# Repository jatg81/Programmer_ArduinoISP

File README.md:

# Programmer_ArduinoISP

This programmer allows to download bootloader and programs to the microprocessor ATMEGA128P (TQFP package).

It has four leds indicator:
  - Blue:   Heartbeat
  - Red:    Error
  - Yellow: Program mode (sending program)
  - Green:  Test led connected to D8

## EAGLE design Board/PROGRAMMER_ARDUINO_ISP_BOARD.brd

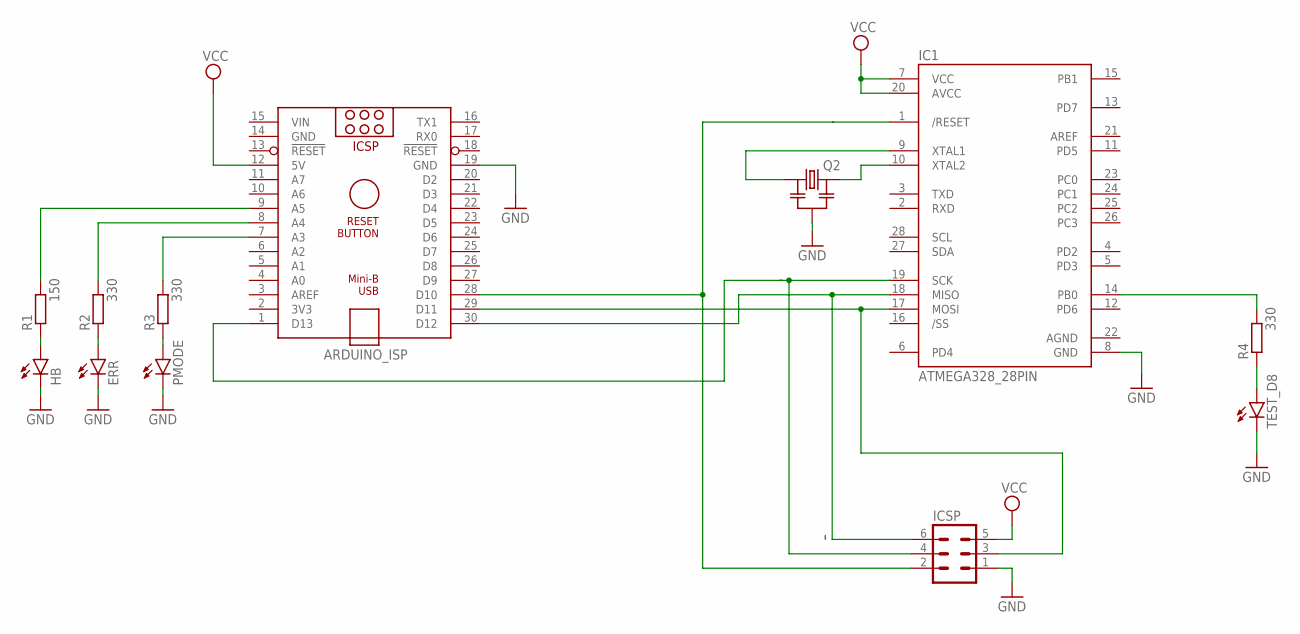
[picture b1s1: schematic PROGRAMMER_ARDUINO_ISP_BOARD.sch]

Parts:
ARDUINO_ISP: ARDUINO_NANO
ERR: LED3MM
HB: LED3MM
IC1: ATMEGA328_28PIN; DIL28-3-R
ICSP: MA03-2
PMODE: LED3MM
Q2: RESONATOR-MURATACST_CE; RESONATOR_MURATA2
R1: 150; R0805
R2, R3, R4: 330; R0805
TEST_D8: 330; LED3MM

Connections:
AGND: IC1.22 (AGND)
GND: ARDUINO_ISP.14 (GND), ARDUINO_ISP.19 (GND), ERR.K (C), HB.K (C), IC1.8 (GND), ICSP.1, PMODE.K (C), Q2.2, TEST_D8.K (C)
unnamed: IC1.9 (XTAL1), Q2.1
unnamed: IC1.10 (XTAL2), Q2.3
unnamed: ARDUINO_ISP.29 (D11), IC1.17 (MOSI), ICSP.3
unnamed: ARDUINO_ISP.30 (D12), IC1.18 (MISO), ICSP.6
unnamed: HB.A, R1.1
unnamed: R4.1, TEST_D8.A
unnamed: ERR.A, R2.1
unnamed: PMODE.A, R3.1
unnamed: ARDUINO_ISP.7 (A3), R3.2
unnamed: ARDUINO_ISP.8 (A4), R2.2
unnamed: ARDUINO_ISP.9 (A5), R1.2
unnamed: IC1.14 (PB0), R4.2
unnamed: ARDUINO_ISP.28 (D10), IC1.1 (/RESET), ICSP.2
unnamed: ARDUINO_ISP.1 (D13), IC1.19 (SCK), ICSP.4
VCC: ARDUINO_ISP.12 (5V), IC1.7 (VCC), IC1.20 (AVCC), ICSP.5
VIN: ARDUINO_ISP.15 (VIN)

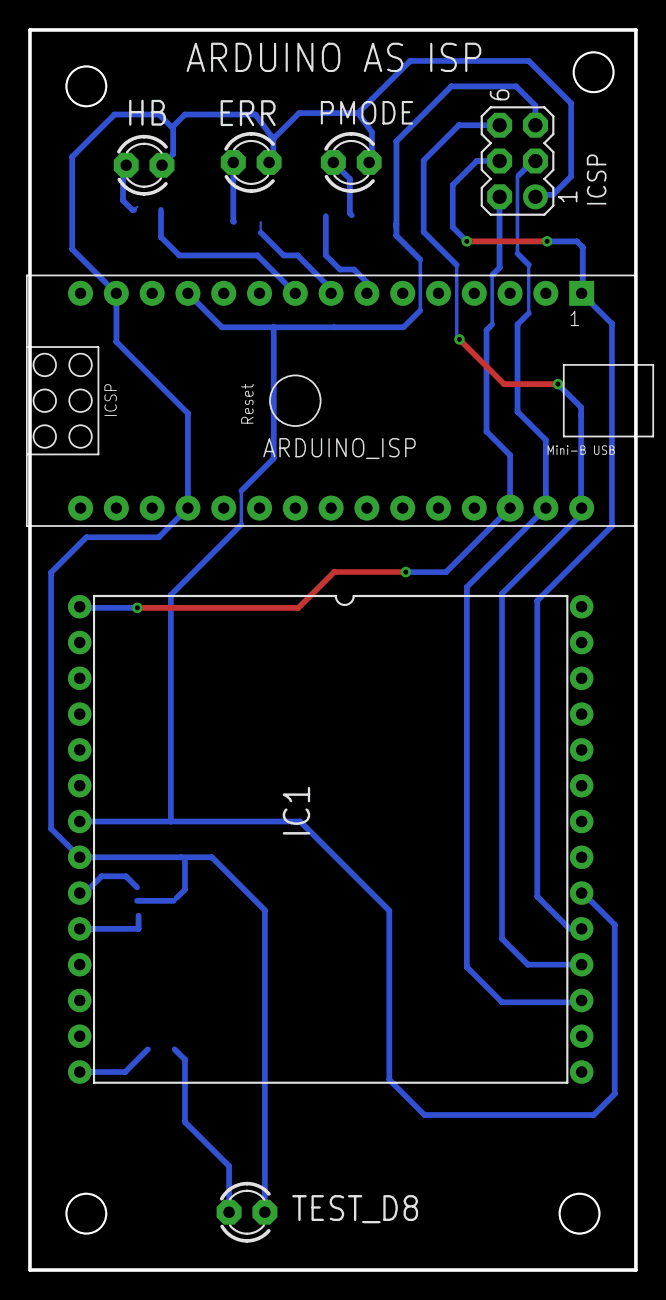
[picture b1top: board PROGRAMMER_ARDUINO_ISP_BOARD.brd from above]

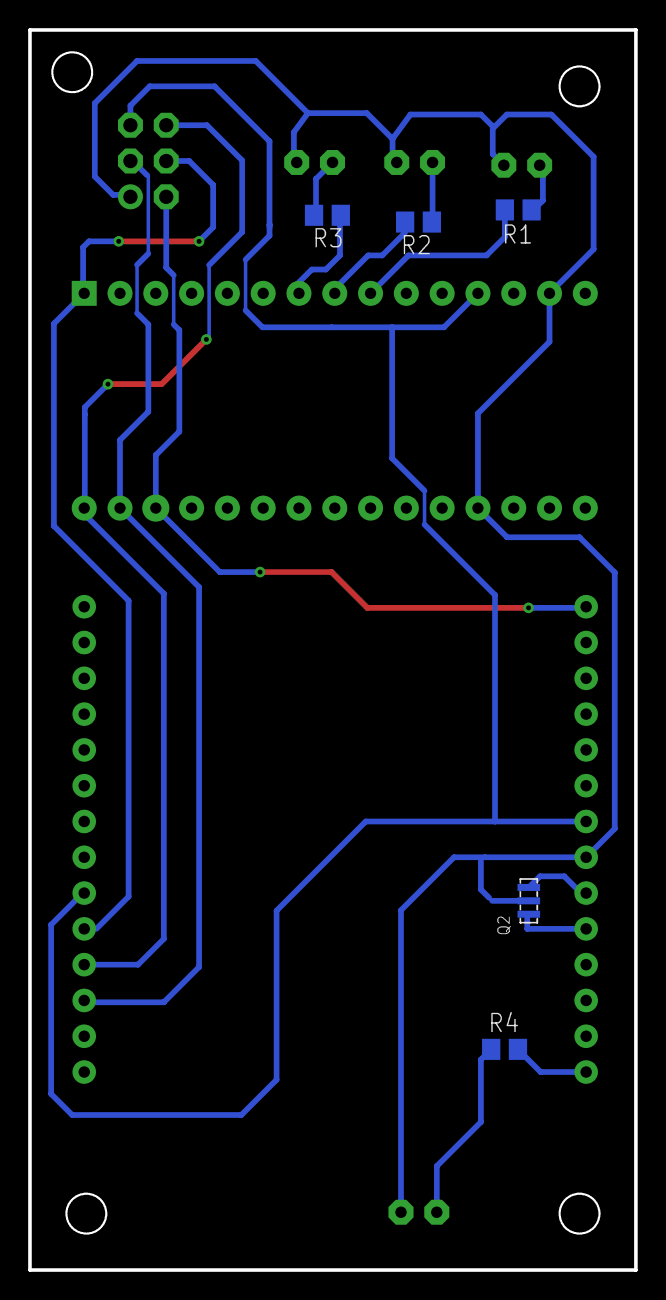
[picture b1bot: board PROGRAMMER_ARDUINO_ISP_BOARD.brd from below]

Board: 2 copper layers, 43.0 x 88.0 mm, 12 parts (5 on the bottom side), 16 nets.

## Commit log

2020-06-21 Create c

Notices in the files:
parts and their libraries:
m-pad-2.1: License : GNU General Public License version 2 (see bottom)
